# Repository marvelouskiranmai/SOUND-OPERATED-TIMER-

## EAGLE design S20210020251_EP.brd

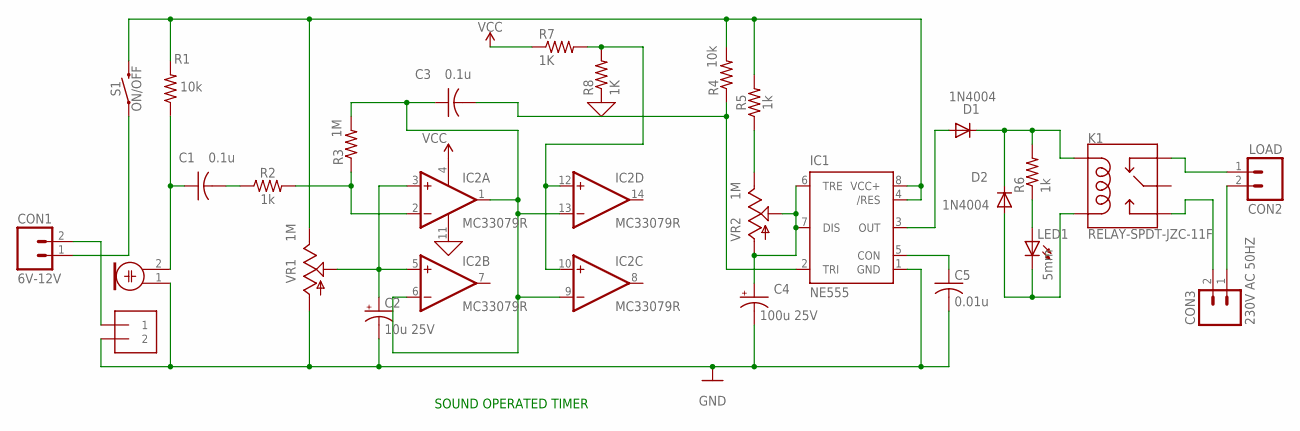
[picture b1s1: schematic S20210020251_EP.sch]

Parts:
C1, C3: 0.1u; C025-024X044
C2: 10u 25V; E2-5
C4: 100u 25V; E3,5-8
C5: 0.01u; C025-024X044
CON1: 6V-12V; 02P
CON2: LOAD; 02P
CON3: 230V AC 50HZ; 02P
D1, D2: 1N4004; DO41-10
IC1: NE555; DIL-08
IC2: MC33079R; SO14
J1: 1X2-3.5MM
K1: RELAY-SPDT-JZC-11F; RELAY-JZC
LED1: 5mm; LED5MM
M1: ELECTRET_MICROPHON-F6035AP; F6035AP
R1, R4: 10k; 0204V
R2, R5: 1k; 0402-TIGHT
R3: 1M; 0204V
R6: 1k; 0204V
R7, R8: 1K; 0204V
S1: ON/OFF; TACTILE_SWITCH_PTH_6.0MM
VR1: 1M; EVUE
VR2: 1M; B64Y

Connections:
0: IC2.11 (V-), R8.1
GND: C2.-, C4.-, C5.2, IC1.1 (GND), J1.2, M1.1, VR1.1 (A)
unnamed: CON2.1, K1.2 (NC)
unnamed: LED1.A, R6.1
unnamed: CON1.2, J1.1
unnamed: D1.A, IC1.3 (OUT)
unnamed: D1.C, D2.C, K1.5 (COIL1), R6.2
unnamed: CON2.2, CON3.1
unnamed: CON1.1, S1.1
unnamed: D2.A, K1.1 (COIL2), LED1.K (C)
unnamed: C5.1, IC1.5 (CON)
unnamed: C4.+, IC1.6 (TRE), IC1.7 (DIS), VR2.A, VR2.S
unnamed: C3.2, IC1.2 (TRI), R4.1
unnamed: C2.+, IC2.3 (+IN), IC2.5 (+IN), VR1.2 (S)
unnamed: R5.1, VR2.E
unnamed: IC2.2 (-IN), R2.2, R3.1
unnamed: IC1.4 (/RES), IC1.8 (VCC+), R1.2, R4.2, R5.2, S1.3 (2), VR1.3 (E)
unnamed: C1.2, R2.1
unnamed: C1.1, M1.2, R1.1
unnamed: CON3.2, K1.3 (NO)
unnamed: C3.1, IC2.1 (OUT), IC2.6 (-IN), IC2.9 (-IN), IC2.13 (-IN), R3.2
unnamed: IC2.10 (+IN), IC2.12 (+IN), R7.2, R8.2
VCC: IC2.4 (V+), R7.1

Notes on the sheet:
SOUND OPERATED TIMER

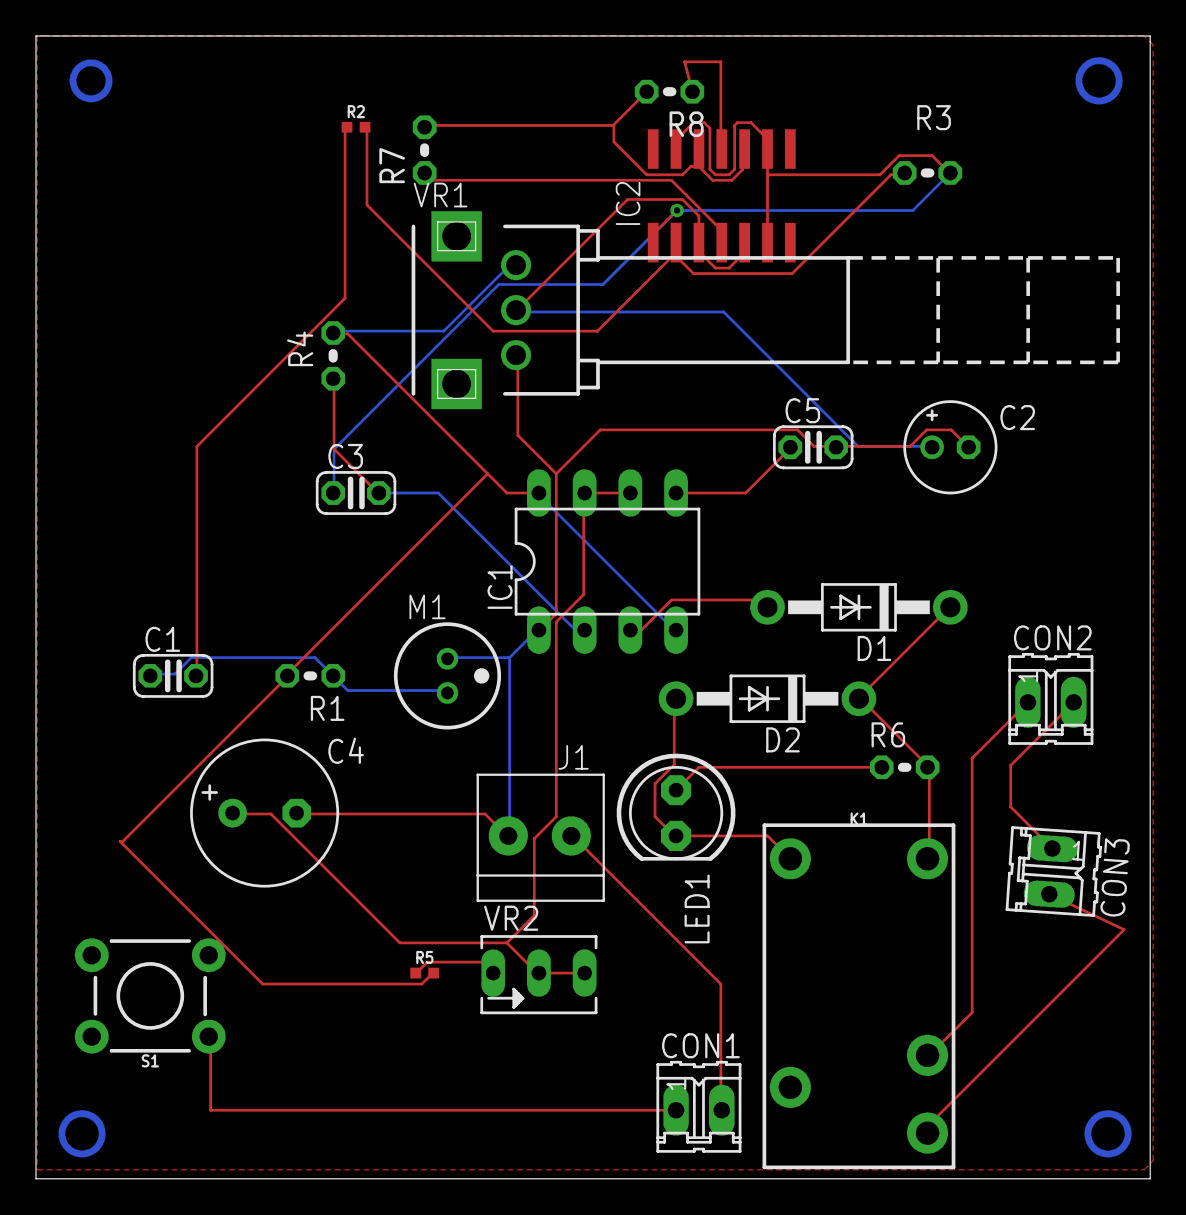
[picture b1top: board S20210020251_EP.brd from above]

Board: 2 copper layers, 61.9 x 63.5 mm, 27 parts (0 on the bottom side), 23 nets.

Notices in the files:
parts and their libraries:
SparkFun-Electromechanical: Licensing: Creative Commons ShareAlike 4.0 International - https://creativecommons.org/licenses/by-sa/4.0
